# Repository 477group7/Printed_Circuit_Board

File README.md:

# Printed_Circuit_Board
The schematic and Eagle implementation of the project's printed circuit board.

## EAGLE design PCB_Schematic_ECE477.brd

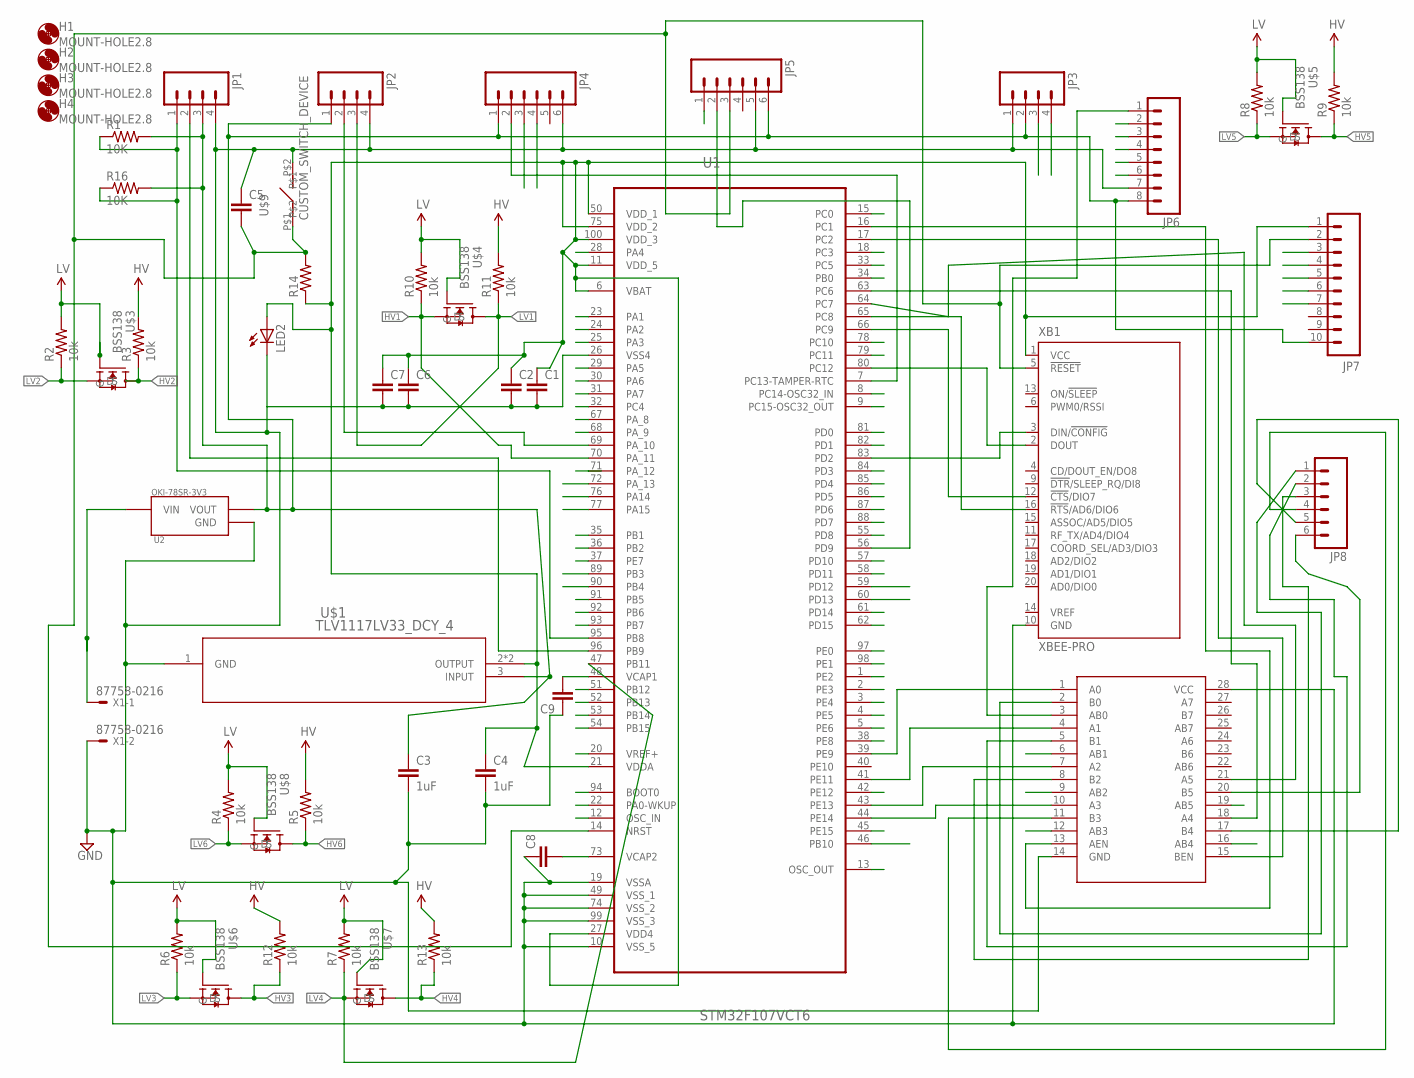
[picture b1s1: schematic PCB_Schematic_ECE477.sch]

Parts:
C1, C2, C5, C6, C7, C8, C9: CAP1206; 1206
C3, C4: 1uF; 1206
H1, H2, H3, H4: MOUNT-HOLE2.8; 2,8
JP1, JP2, JP3: M04PTH; 1X04
JP4, JP5, JP8: M06SILK_FEMALE_PTH; 1X06
JP6: M08SILK_FEMALE_PTH; 1X08
JP7: M10SILK_FEMALE_PTH; 1X10
LED2: LED_E; LED_1206
R1, R16: 10K; 1206
R2, R3, R4, R5, R6, R7, R8, R9, R10, R11, R12, R13: 10k; 1206
R14: RESISTOR1206; 1206
U1: STM32F107VCT6; QFP50P1600X1600X160-100N
U2: OKI-78SR_3V3_SMPS; SMPS_MODULE
U$1: TLV1117LV33_DCY_4; DCY4
U$2: MUX_DEVMUX_VAR_1; QSOP28
U$3, U$4, U$5, U$6, U$7, U$8: BSS138
U$9: CUSTOM_SWITCH_DEVICE; CUSTOM_SWITCH_PACKAGE
X1: 87758-0216
XB1: XBEE-PRO

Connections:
GND: C1.2, C2.2, C3.2, C4.2, C5.1, C6.2, C7.2, C8.1, C9.1, JP1.4, JP2.4, JP3.1, JP4.6, JP5.5, JP6.7, LED2.C, U1.10 (VSS_5), U1.19 (VSSA), U1.26 (VSS4), U1.49 (VSS_1), U1.74 (VSS_2), U1.99 (VSS_3), U2.GND, U$1.1 (GND), U$2.14 (GND), U$2.28 (VCC), U$9.P$2, X1.2, XB1.10 (GND)
HV: C3.1, JP1.3, JP2.1, JP3.2, JP4.1, JP5.6, JP6.8, JP7.10, R1.2, R3.2, R5.2, R9.2, R11.2, R12.2, R13.2, R16.2, U2.VOUT, U$1.3 (INPUT)
HV1: R10.1, U1.70 (PA_11), U$4.S
HV2: JP3.3, R3.1, U$3.D
HV3: JP4.3, R12.1, U$6.D
HV4: JP4.4, R13.1, U$7.D
HV5: JP5.1, R9.1, U$5.D
HV6: JP3.4, R5.1, U$8.D
LV: R2.2, R4.2, R6.2, R7.2, R8.2, R10.2, U$3.G, U$4.G, U$5.G, U$6.G, U$7.G, U$8.G
LV1: JP2.3, R11.1, U$4.D
LV2: R2.1, U1.59 (PD12), U$3.S
LV3: R6.1, U1.46 (PB10), U$6.S
LV4: R7.1, U1.47 (PB11), U$7.S
LV5: R8.1, U1.55 (PD8), U$5.S
LV6: R4.1, U1.60 (PD13), U$8.S
unnamed: C8.2, U1.73 (VCAP2)
unnamed: JP2.2, U1.69 (PA_10)
unnamed: JP6.6, U$2.19 (AB5)
unnamed: JP1.2, U1.96 (PB9)
unnamed: JP6.2, U$2.6 (AB1)
unnamed: JP6.3, U$2.9 (AB2)
unnamed: JP1.1, R1.1, R16.1, U1.95 (PB8)
unnamed: JP5.2, U1.56 (PD9)
unnamed: JP4.2, U1.7 (PC13-TAMPER-RTC)
unnamed: C9.2, U1.48 (VCAP1)
unnamed: JP7.7, U1.90 (PB4)
unnamed: JP7.6, U1.76 (PA14)
unnamed: JP7.3, U1.77 (PA15)
unnamed: JP7.5, U1.89 (PB3)
unnamed: JP7.4, U1.72 (PA_13)
unnamed: U2.VIN, X1.1
unnamed: U1.80 (PC12), XB1.2 (DOUT)
unnamed: U1.66 (PC9), XB1.12 (!CTS!/DIO7)
unnamed: U1.65 (PC8), XB1.16 (!RTS!/AD6/DIO6)
unnamed: U1.83 (PD2), XB1.3 (DIN/!CONFIG)
unnamed: U1.16 (PC1), U$2.13 (AEN)
unnamed: U1.17 (PC2), U$2.15 (BEN)
unnamed: U1.39 (PE9), U$2.1 (A0)
unnamed: U1.41 (PE11), U$2.4 (A1)
unnamed: U1.43 (PE13), U$2.7 (A2)
unnamed: U1.44 (PE14), U$2.10 (A3)
unnamed: U1.63 (PC6), U$2.18 (A4)
unnamed: U1.64 (PC7), U$2.21 (A5)
unnamed: JP8.1, U$2.2 (B0)
unnamed: JP8.2, U$2.5 (B1)
unnamed: JP8.3, U$2.8 (B2)
unnamed: JP8.4, U$2.11 (B3)
unnamed: JP8.5, U$2.17 (B4)
unnamed: JP8.6, U$2.20 (B5)
unnamed: JP6.1, U$2.3 (AB0)
unnamed: JP6.4, U$2.12 (AB3)
unnamed: JP6.5, U$2.16 (AB4)
RESET_OUT: C5.2, JP5.3, JP7.2, R14.2, U1.14 (NRST), U$9.P$1, XB1.5 (!RESET)
VIN_MICRO_3.3: C1.1, C2.1, C4.1, C6.1, C7.1, JP7.1, LED2.A, R14.1, U1.6 (VBAT), U1.11 (VDD_5), U1.21 (VDDA), U1.27 (VDD4), U1.50 (VDD_1), U1.75 (VDD_2), U1.100 (VDD_3), U$1.2 (OUTPUT), U$1.4 (OUTPUT), XB1.1 (VCC)

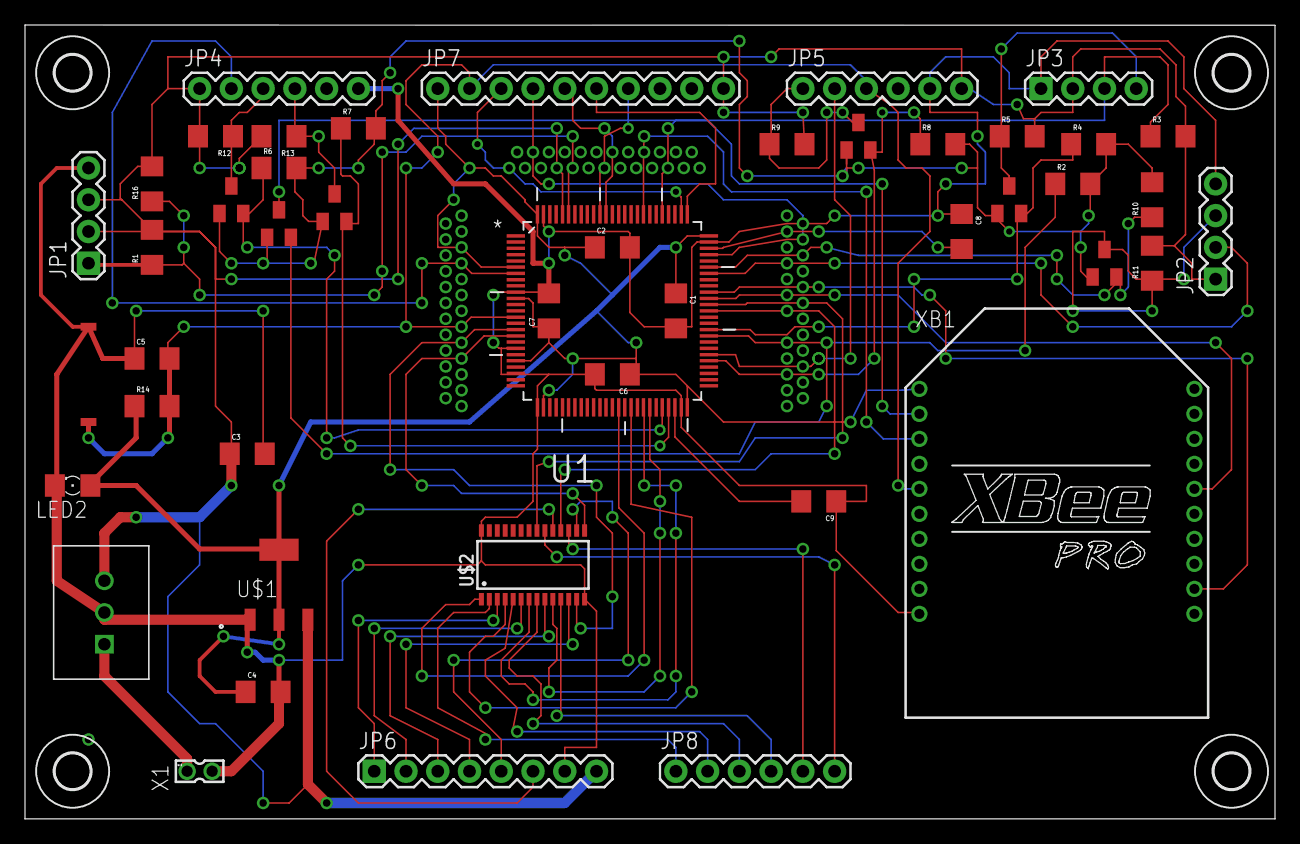
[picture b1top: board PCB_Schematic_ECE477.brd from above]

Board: 2 copper layers, 100.0 x 63.5 mm, 50 parts (0 on the bottom side), 54 nets.

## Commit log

2015-10-07 Added PCB Files.
2015-10-16 Updated PCB
2015-10-21 Latest Schematics

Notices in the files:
parts and their libraries:
SparkFun-Passives: Licensing: Creative Commons ShareAlike 4.0 International - https://creativecommons.org/licenses/by-sa/4.0
